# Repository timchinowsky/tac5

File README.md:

# tac5

This repo describes PCBs and rp2040/rp2350 CircuitPython support for TI's [TAC5xxx](https://www.ti.com/product/TAC5212) audio codecs.  This code depends on extensions to CircuitPython's `rp2pio` library found in https://github.com/adafruit/circuitpython/pull/9659.

* [`pcm.py`](pcm.py) uses the rp2 PIO to implement a PCM interface to the TAC5 which supports arbitrary numbers of channels, word sizes, and sample rates.

* [`tac5.py`](tac5.py) implements a TAC5 class which knows how to initialize the TAC5xxx over I2C, write to its DACs, and read from its ADCs.

* If multiple TAC5xxx parts with different I2C addresses are present, they are assumed to be wired in parallel for multichannel operation and [configured]( https://docs.google.com/spreadsheets/d/1LnI_OwJfJHtquBkj7qKH8Fg3jmsCv9cRniIS2uqMfjU/edit?usp=sharing) appropriately.  In this mode, each chip uses one time slot
in the DOUT signal and makes its DOUT Hi-Z at other times.  

* Chips are mounted on [breakout boards](https://www.pcbway.com/project/shareproject/Breakout_board_for_the_TI_TAC5212_audio_codec_ecc0a61b.html).  KiCad files for these boards are [here](pcb).  Schematic and layout look like this:

## Playing multichannel audio files

If you have [speakers](speakers) attached to the codecs, [multi-track audio files](samples) stored on an SD card accessible to the rp2040 can be played on the codecs as follows:

```python
Adafruit CircuitPython 9.1.0-beta.3-252-g10dfea4284-dirty on 2024-11-07; Adafruit Feather RP2040 with rp2040
>>> import tac5
>>> t=tac5.TAC5()
>>> t.play('/count_8ch_32bit_16000Hz.raw')
playing...
opening /count_8ch_32bit_16000Hz.raw ...
repeating...
repeating...
repeating...
...
```

## Codec test, analog loopback

In this example, 4 TAC5212's are connected with BCLK, FSYNC, DOUT, DIN, SCL, and SDA in parallel, and on each chip, the differential DAC outputs are connected to the differential ADC inputs to provide test signals for the ADCs, i.e. OUT1P -> IN1P, OUT1M -> IN1M, OUT2P -> IN2P, OUT2M -> IN2M.

```python
Adafruit CircuitPython 9.1.0-beta.3-76-g2f62612186-dirty on 2024-07-18; Adafruit Feather RP2040 with rp2040
>>> 
>>> import tac5
>>> t = tac5.TAC5()
>>> t.play()
playing...
>>> t.record()
sample,record0,record1,record2,record3,record4,record5,record6,record7,
0,-1,-1,-1,-1,-21642,13829,-311,-14878,
1,22355,-20880,-14861,22749,-19762,8760,6829,-20253,
2,21608,-13819,-15930,23037,-17183,3144,13306,-22783,
3,18190,-3347,-16936,22962,-13994,-2666,18482,-22111,
4,10858,7951,-17876,22524,-10311,-8313,21849,-18332,
5,602,17291,-18745,21730,-6263,-13440,23074,-11979,
6,-8849,22352,-19541,20593,-1995,-17725,22040,-3945,
7,-17070,21881,-20257,19131,2341,-20896,18845,4634,
8,-21748,15993,-20896,17368,6597,-22754,13806,12577,
9,-22490,6149,-21452,15331,10620,-23182,7417,18743,
...(115 more lines)
```

When called without arguments, `play()` creates test output (right now sine waves of various frequencies separated by gaps) for each DAC channel and sets up the interface to repeatedly send the data to the DACs in the background.
When `record()` is called without arguments, it creates a buffer the same size as the playing buffer, fills it with ADC samples, and prints out the returned data in
CSV format.  The table below compares the DAC outputs as seen on a scope with the ADC outputs plotted on a spreadsheet:

| DAC output |  &nbsp; &nbsp; &nbsp; &nbsp; &nbsp; &nbsp; &nbsp; &nbsp; &nbsp; &nbsp; &nbsp; &nbsp; &nbsp; &nbsp; &nbsp;&nbsp; &nbsp; &nbsp;  | ADC output |
| ---------- | ---- |---------- |
|    | |  |

## Digital loopback test, no codec, single buffered

* This example shows how a loopback test can be used to test streaming data transfer when if a codec is not present.  Connect DOUT to DIN.

```python
Adafruit CircuitPython 9.1.0-beta.0-426-g65556b42a5 on 2025-01-27; Adafruit Feather RP2350 with rp2350a
>>> 
>>> import tac5
>>> t = tac5.TAC5(channels=2, width=8, sample_rate=12000, address=None)
>>> t.rec(length=10)
recording...
>>> t.play(length=10, init='count')
playing...
>>> t.show(t.record_loop_buffer)
'sample'; 'ch0'; 'ch1'
0; -10; -9
1; -7; -6
2; -5; -4
3; -4; -3
4; -2; -1
5; 1; 2
6; 2; 3
7; 4; 5
8; 7; 8
9; 9; 10
>>> t.show(t.play_loop_buffer, shift=False)
'sample'; 'ch0'; 'ch1'
0; -10; -9
1; -8; -7
2; -6; -5
3; -4; -3
4; -2; -1
5; 0; 1
6; 2; 3
7; 4; 5
8; 6; 7
9; 8; 9
>>> 
```

## Digital loopback test, no codec, double buffered

Note that the `count` test data generated by `tac5` is offset by 1 in `play_loop2_buffer` to distinguish it from the other buffer's data. 

```python
Adafruit CircuitPython 9.1.0-beta.0-426-g65556b42a5 on 2025-01-27; Adafruit Feather RP2350 with rp2350a
>>> 
>>> import tac5
>>> t = tac5.TAC5(channels=2, width=8, sample_rate=12000, address=None)
>>> t.rec(length=10, double_buffer=True)
recording...
>>> t.play(length=10, init='count', double_buffer=True)
playing...
>>> t.show(t.record_loop_buffer)
'sample'; 'ch0'; 'ch1'
0; -10; -9
1; -8; -7
2; -6; -5
3; -4; -3
4; -2; -1
5; 0; 1
6; 2; 3
7; 4; 5
8; 6; 7
9; 8; 9
>>> t.show(t.record_loop2_buffer)
'sample'; 'ch0'; 'ch1'
0; -9; -8
1; -7; -6
2; -5; -4
3; -3; -2
4; -1; 0
5; 1; 2
6; 3; 4
7; 5; 6
8; 7; 8
9; 9; 10
>>> t.show(t.play_loop_buffer, shift=False)
'sample'; 'ch0'; 'ch1'
0; -10; -9
1; -8; -7
2; -6; -5
3; -4; -3
4; -2; -1
5; 0; 1
6; 2; 3
7; 4; 5
8; 6; 7
9; 8; 9
>>> t.show(t.play_loop2_buffer, shift=False)
'sample'; 'ch0'; 'ch1'
0; -9; -8
1; -7; -6
2; -5; -4
3; -3; -2
4; -1; 0
5; 1; 2
6; 3; 4
7; 5; 6
8; 7; 8
9; 9; 10
>>> 
```

## Digital loopback test, no codec, double buffered, recording to "tape"

```python
Adafruit CircuitPython 9.1.0-beta.3-180-geda524f85c-dirty on 2024-10-24; Adafruit Feather RP2040 with rp2040
>>> import tac5
>>> t = tac5.TAC5(channels=2, width=8, sample_rate=12000, address=None)
>>> t.rec(length=10, double_buffer=True)
recording...
>>> t.play(length=10, test='count', double_buffer=True)
playing...
>>> t.show(t.record_loop_buffer)
'sample'; 'ch0'; 'ch1'
0; -9; -8
1; -7; -6
2; -5; -4
3; -3; -2
4; -1; 0
5; 1; 2
6; 3; 4
7; 5; 6
8; 7; 8
9; 9; 10
>>> t.tape('/foo.txt')
Traceback (most recent call last):
  File "<stdin>", line 1, in <module>
  File "tac5.py", line 347, in tape
KeyboardInterrupt: 
>>> import os
>>> os.stat('/foo.txt')
(32768, 0, 0, 0, 0, 0, 767760, 946685390, 946685390, 946685390)
```

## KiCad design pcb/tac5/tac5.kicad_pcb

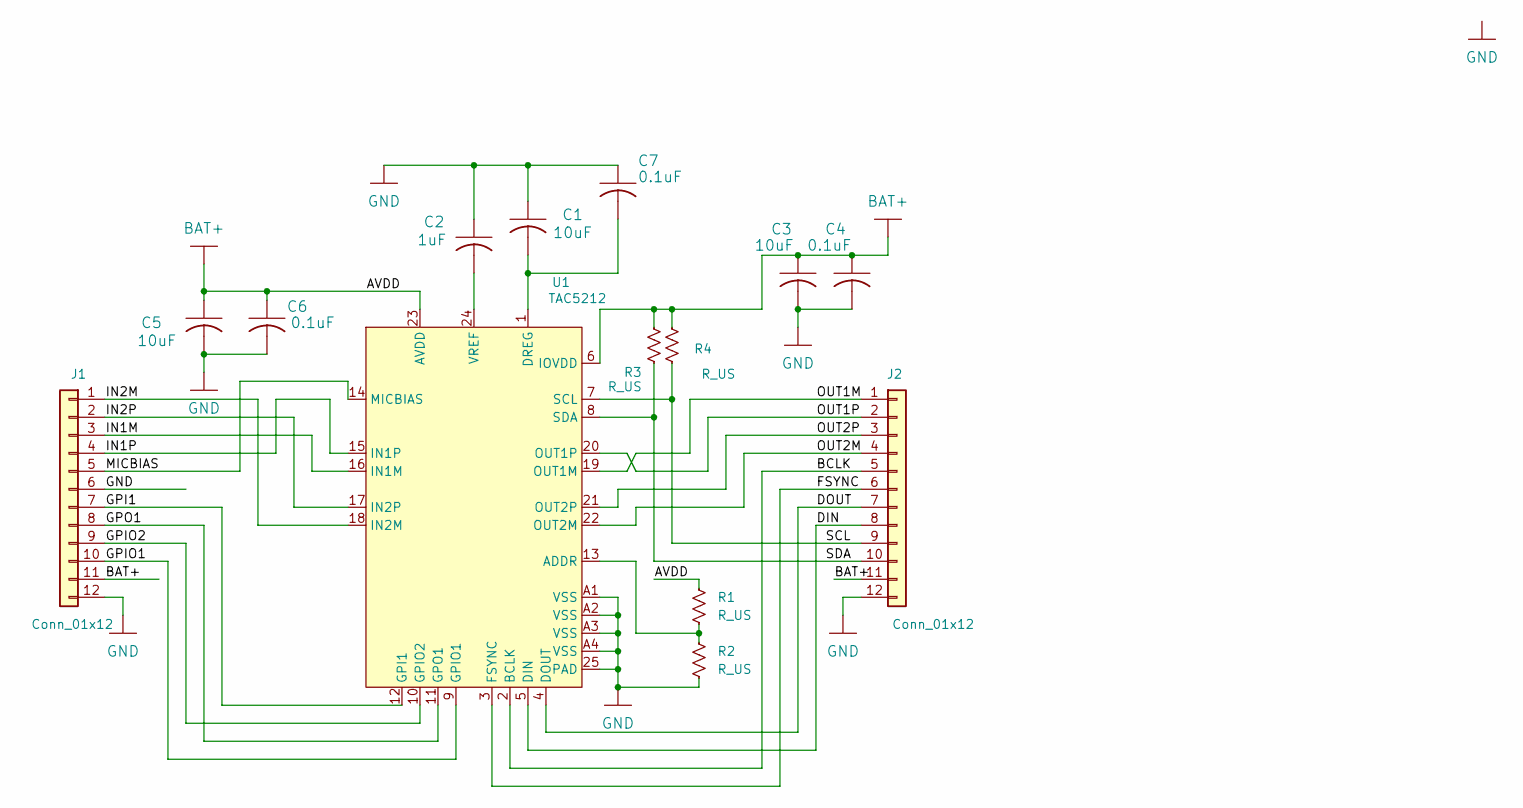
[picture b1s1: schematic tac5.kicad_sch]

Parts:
C1, C3, C5: 10uF; C_0603_1608Metric; MPN RC0402FR-070RL
C2: 1uF; C_0603_1608Metric; MPN RC0402FR-070RL
C4, C6, C7: 0.1uF; C_0603_1608Metric; MPN RC0402FR-070RL
J1, J2: Conn_01x12; PinHeader_1x12_P2.54mm_Vertical
R1, R2, R3, R4: R_US; R_0603_1608Metric
U1: TAC5212; VQFN-24-1EP_4x4mm_P0.5mm_EP2.45x2.45mm_ThermalVias

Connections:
/BCLK: J2.5, U1.2 (BCLK)
/DIN: J2.8, U1.5 (DIN)
/DOUT: J2.7, U1.4 (DOUT)
/FSYNC: J2.6, U1.3 (FSYNC)
/GPI1: J1.7, U1.12 (GPI1)
/GPIO1: J1.10, U1.9 (GPIO1)
/GPIO2: J1.9, U1.10 (GPIO2)
/GPO1: J1.8, U1.11 (GPO1)
/IN1M: J1.3, U1.16 (IN1M)
/IN1P: J1.4, U1.15 (IN1P)
/IN2M: J1.1, U1.18 (IN2M)
/IN2P: J1.2, U1.17 (IN2P)
/MICBIAS: J1.5, U1.14 (MICBIAS)
/OUT1M: J2.1, U1.19 (OUT1M)
/OUT1P: J2.2, U1.20 (OUT1P)
/OUT2M: J2.4, U1.22 (OUT2M)
/OUT2P: J2.3, U1.21 (OUT2P)
/SCL: J2.9, R4.1, U1.7 (SCL)
/SDA: J2.10, R3.1, U1.8 (SDA)
BAT+: C3.1, C4.1, C5.1, C6.1, J1.11, J2.11, R1.2, R3.2, R4.2, U1.6 (IOVDD), U1.23 (AVDD)
GND: C1.1, C2.1, C3.2, C4.2, C5.2, C6.2, C7.1, J1.6, J1.12, J2.12, R2.1, U1.25 (PAD), U1.A1 (VSS), U1.A2 (VSS), U1.A3 (VSS), U1.A4 (VSS)
unnamed: R1.1, R2.2, U1.13 (ADDR)
unnamed: C1.2, C7.2, U1.1 (DREG)
unnamed: C2.2, U1.24 (VREF)

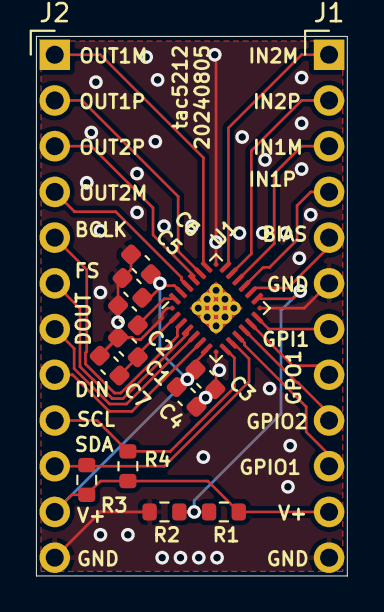
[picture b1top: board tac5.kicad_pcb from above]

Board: 2 copper layers, 17.3 x 30.0 mm, 14 parts (0 on the bottom side), 24 nets.

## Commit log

2024-08-28 add files
2024-08-28 Add PCBWay link to README.md
2024-09-24 add background record
2024-09-26 add frame blocking, input streaming, loopback example
2024-09-27 improve show method
2024-10-24 add support for double buffering
2024-10-24 add tape function and example
2024-11-05 add play_raw, speaker mount
2024-11-06 add stl
2024-11-06 fix typos
2024-11-07 add samples
2024-11-12 add samples, processing examples
2025-01-27 fix loopback tests
